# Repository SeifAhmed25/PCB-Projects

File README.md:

# Seif Ahmed - PCB Design Portfolio

This repository showcases my practical work in **PCB design**, focusing on **schematic creation**, **PCB layout**, and **manufacturing optimization** using **KiCad** software.

Projects are arranged from **latest to oldest**.

**Tools & Skills:**  
KiCad • Circuit Design • PCB Layout • DRC/ERC Checks • Soldering • Git Version Control • Documentation

---

## MCU Datalogger

**Goal:**  
Design a printed circuit board for a microcontroller-based data logger using the **ATmega328P-AU**, supported by two **EEPROMs** and a **real-time clock (RTC)**.

**Key Features:**
- Designed in two versions: a **2-layer** and a **4-layer** PCB, both managed using **Git** version control.  
- The **ATmega328P-AU** acts as the central controller.  
- Handles communication with the **RTC** and **EEPROM** modules.  
- Includes indicator LEDs and a reset circuit for the microcontroller.

**Main Components:**
- ATmega328P-AU  
- Crystal oscillator  
- Battery  
- Capacitors (decoupling)  
- Resistors  

**Project Pictures:**  
- **Board Schematic**  
    
- **Board Layout**  
    
- **Board Top View**  
    
- **Board Back View**  

---

## Solar Power Supply PCB

**Goal:**  
Design and implement a PCB that delivers a **regulated 3.3 V output** from a **solar panel**, functioning as a **solar energy regulator module**.  
This circuit was originally designed by *Elektor Magazine* and reimplemented in **KiCad**.

**Key Features:**
- Converts unregulated solar panel voltage into regulated **3.3 V**.  
- Suitable for powering **microcontrollers and sensors**.  
- Includes **copper fills** and a mix of **THT and SMD components**.

**Main Components:**
- Male connectors  
- Protection diodes  
- Inductor (switching regulator)  
- DC-DC converter  
- Resistors  

**Project Pictures:**  
- **Board Schematic**  
    
- **Board Top View**  
    
- **Board Back View**  

---

## Breadboard Power Supply PCB

**Goal:**  
Design a compact PCB that plugs directly into a **breadboard** and provides **5 V** and **3.3 V** regulated outputs.

**Key Features:**
- Fits perfectly on a standard breadboard.  
- Provides both **5 V** and **3.3 V** outputs.  
- Includes an **on/off switch** and **copper fills**.  
- Assembled using **THT components** for ease of soldering.

**Main Components:**
- Capacitors  
- LED  
- Jack connector  
- Screw terminals  
- Male connectors  
- Resistors  
- Slide switch  
- Voltage regulators  

**Project Pictures:**  
- **Board Schematic**  
    
- **Board Top View**  
    
- **Board Back View**  

---

## LED Torch PCB

**Goal:**  
An introductory project for learning **KiCad** fundamentals through schematic capture, PCB layout, and basic 3D visualization.

**Key Features:**
- Simple LED lighting circuit.  
- Demonstrates PCB routing and footprint placement.  
- Serves as a base for learning design rules and 3D viewer tools.

**Main Components:**
- Battery  
- Switch  
- Resistor  
- LED  

**Project Pictures:**  
- **Board Top View**  
    
- **Board Back View**  

---

**Author:** Seif Ahmed  
**Contact:** [Email](mailto:seif7760@gmail.com)  
**Software Used:** KiCad 9.0

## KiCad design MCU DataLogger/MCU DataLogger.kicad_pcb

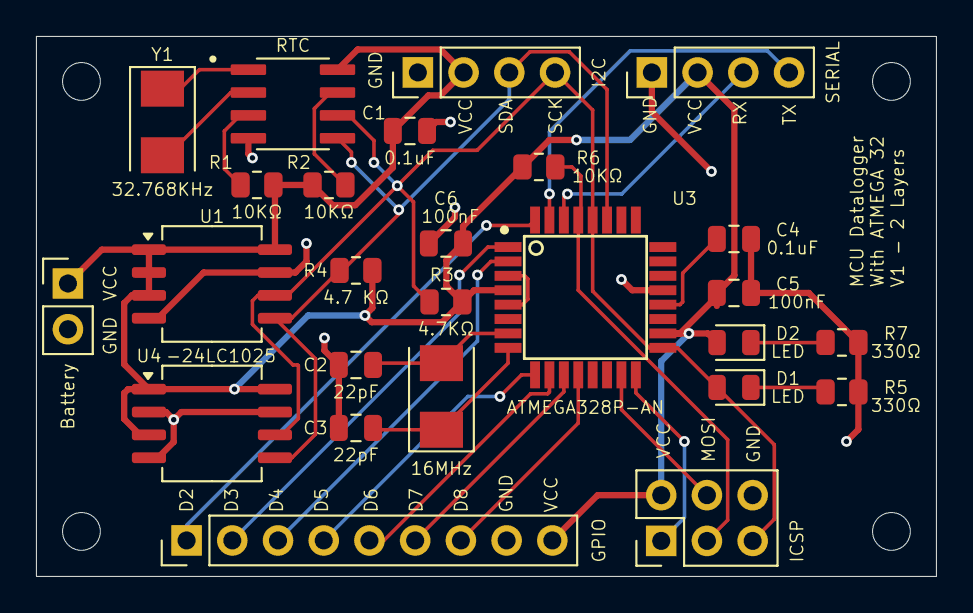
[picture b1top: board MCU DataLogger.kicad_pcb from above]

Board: 2 copper layers, 50.0 x 30.0 mm, 30 parts (0 on the bottom side), 26 nets.

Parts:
Battery: Battery; PinHeader_1x02_P2.54mm_Vertical
C1, C4: 0.1uF; C_0805_2012Metric
C2, C3: 22pF; C_0805_2012Metric
C5, C6: 100nF; C_0805_2012Metric
D1, D2: LED; LED_0805_2012Metric
GPIO: Conn_01x09_Pin; PinHeader_1x09_P2.54mm_Vertical
H1, H2, H3, H4: MountingHole; MountingHole_2.1mm
I2C: Conn_01x04_Pin; PinHeader_1x04_P2.54mm_Vertical
ICSP: Conn_02x03_Odd_Even; PinHeader_2x03_P2.54mm_Vertical
R1, R2, R6: 10KΩ; R_0805_2012Metric
R3: 4.7KΩ; R_0805_2012Metric
R4: 4.7 KΩ; R_0805_2012Metric
R5, R7: 330Ω; R_0805_2012Metric
RTC: DS1337S_; SOIC127P600X175-8N
SERIAL: Conn_01x04_Pin; PinHeader_1x04_P2.54mm_Vertical
U1, U4: -24LC1025; SOIC-8_5.3x6.2mm_P1.27mm
U3: ATMEGA328P-AN; QFP80P900X900X120-32N
Y1: 32.768KHz; Crystal_SMD_5032-2Pin_5.0x3.2mm
Y2: 16MHz; Crystal_SMD_5032-2Pin_5.0x3.2mm

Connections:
/D2: GPIO.1, U3.32 (PD2)
/D3: GPIO.2, U3.1 (PD3)
/D4: GPIO.3, U3.2 (PD4)
/D5: GPIO.4, U3.9 (PD5)
/D6: GPIO.5, U3.10 (PD6)
/D7: GPIO.6, U3.11 (PD7)
/D8: GPIO.7, U3.12 (PB0)
/MISO: ICSP.1, U3.16 (PB4)
/MOSI: ICSP.4, U3.15 (PB3)
/RESET: ICSP.3, R6.1, U3.29 (PC6/~RESET)
/RX: SERIAL.3, U3.30 (PD0)
/SCK: D1.2 (A), I2C.4, ICSP.5, R3.2, RTC.6 (SCL), U1.6 (SCL), U3.17 (PB5), U3.28 (PC5), U4.6 (SCL)
/SDA: I2C.3, R4.2, RTC.5 (SDA), U1.5 (SDA), U3.27 (PC4), U4.5 (SDA)
/TX: SERIAL.4, U3.31 (PD1)
/VCC: Battery.1 (+), C1.1, C5.1, C6.1, D2.2 (A), GPIO.9, I2C.2, ICSP.2, R1.1, R2.1, R3.1, R4.1, R6.2, RTC.8 (VCC), SERIAL.2, U1.1 (A0), U1.2 (A1), U1.3 (A2), U1.8 (VCC), U3.4 (VCC), U3.18 (AVCC), U4.1 (A0), U4.3 (A2), U4.8 (VCC)
GND: Battery.2 (-), C1.2, C2.1, C3.1, C4.1, C5.2, C6.2, GPIO.8, I2C.1, ICSP.6, R5.1, R7.2, RTC.4 (GND), SERIAL.1, U1.4 (GND), U1.7 (WP), U3.21 (GND), U4.2 (A1), U4.4 (GND), U4.7 (WP)
unnamed: D1.1 (K), R5.2
unnamed: D2.1 (K), R7.1
unnamed: R2.2, RTC.7 (SQW/~INT)
unnamed: RTC.1 (X1), Y1.1
unnamed: RTC.2 (X2), Y1.2
unnamed: R1.2, RTC.3 (~INTA)
unnamed: C4.2, U3.20 (AREF)
unnamed: U3.3 (GND), U3.5 (GND)
unnamed: C2.2, U3.7 (PB6), Y2.2
unnamed: C3.2, U3.8 (PB7), Y2.1

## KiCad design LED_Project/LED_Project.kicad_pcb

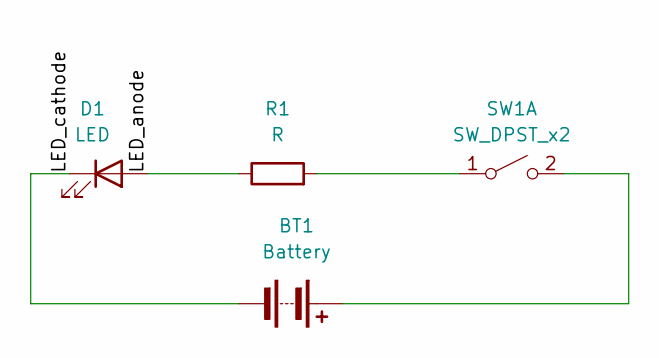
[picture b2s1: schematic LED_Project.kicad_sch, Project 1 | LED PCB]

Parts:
BT1: Battery; BatteryHolder_Keystone_105_1x2430
D1: LED; LED_D5.0mm
R1: R; R_Axial_DIN0204_L3.6mm_D1.6mm_P7.62mm_Horizontal
SW1: SW_DPST_x2; SW_TH_Tactile_Omron_B3F-10xx

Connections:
/LED_anode: D1.2 (A), R1.1
/LED_cathode: BT1.2 (-), D1.1 (K)
unnamed: BT1.1 (+), SW1.2 (B)
unnamed: R1.2, SW1.1 (A)

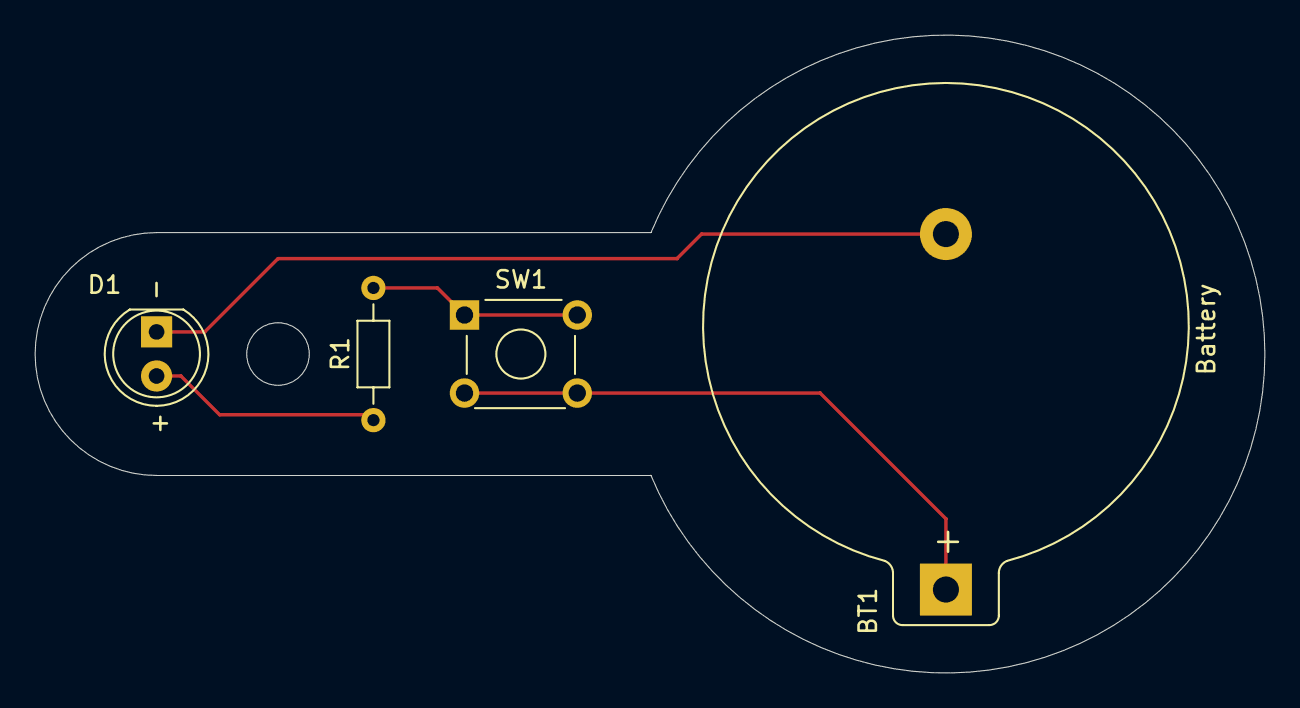
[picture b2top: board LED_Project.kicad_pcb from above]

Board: 2 copper layers, 70.9 x 36.8 mm, 4 parts (0 on the bottom side), 4 nets.

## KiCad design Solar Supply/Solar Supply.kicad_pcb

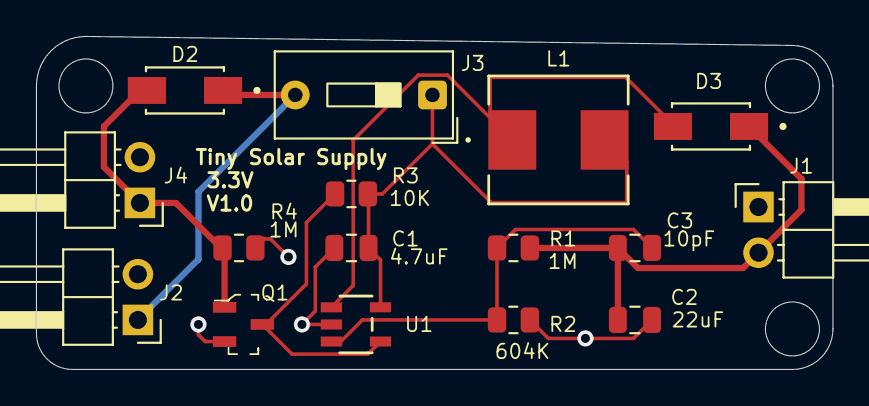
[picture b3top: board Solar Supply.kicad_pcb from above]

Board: 2 copper layers, 44.2 x 18.5 mm, 16 parts (0 on the bottom side), 8 nets.

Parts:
C1: 4.7uF; C_0805_2012Metric
C2: 22uF; C_0805_2012Metric
C3: 10pF; C_0805_2012Metric
D2, D3: SS14; DIOM4325X250N
J1, J2, J4: Conn_01x02_Pin; PinHeader_1x02_P2.54mm_Horizontal
J3: Conn_01x02_Pin; SW_DIP_SPSTx01_Slide_9.78x4.72mm_W7.62mm_P2.54mm
L1: ASPI-0630LR-100M-T15; IND_ASPI-0630LR_ABR
Q1: 2N7002; SOT-23-3
R1, R4: 1M; R_0805_2012Metric
R2: 604K; R_0805_2012Metric
R3: 10K; R_0805_2012Metric
U1: AP3015AKTR-G1; SOT23-5_1P55X2P9_DIO

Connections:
/Battery_P: D2.C, J2.1, J3.2
/Out_P: C2.1, C3.1, D3.C, J1.2, R1.1
/Solar_P: D2.A, J4.1, Q1.1 (G), R4.1
GNDD: C1.2, C2.2, J1.1, J2.2, J4.2, Q1.2 (S), R2.2, R4.2, U1.2 (GND)
unnamed: C1.1, J3.1, L1.2, R3.1, U1.5 (VIN)
unnamed: Q1.3 (D), R3.2, U1.4 (SHDN)
unnamed: C3.2, R1.2, R2.1, U1.3 (FB)
unnamed: D3.A, L1.1, U1.1 (SW)

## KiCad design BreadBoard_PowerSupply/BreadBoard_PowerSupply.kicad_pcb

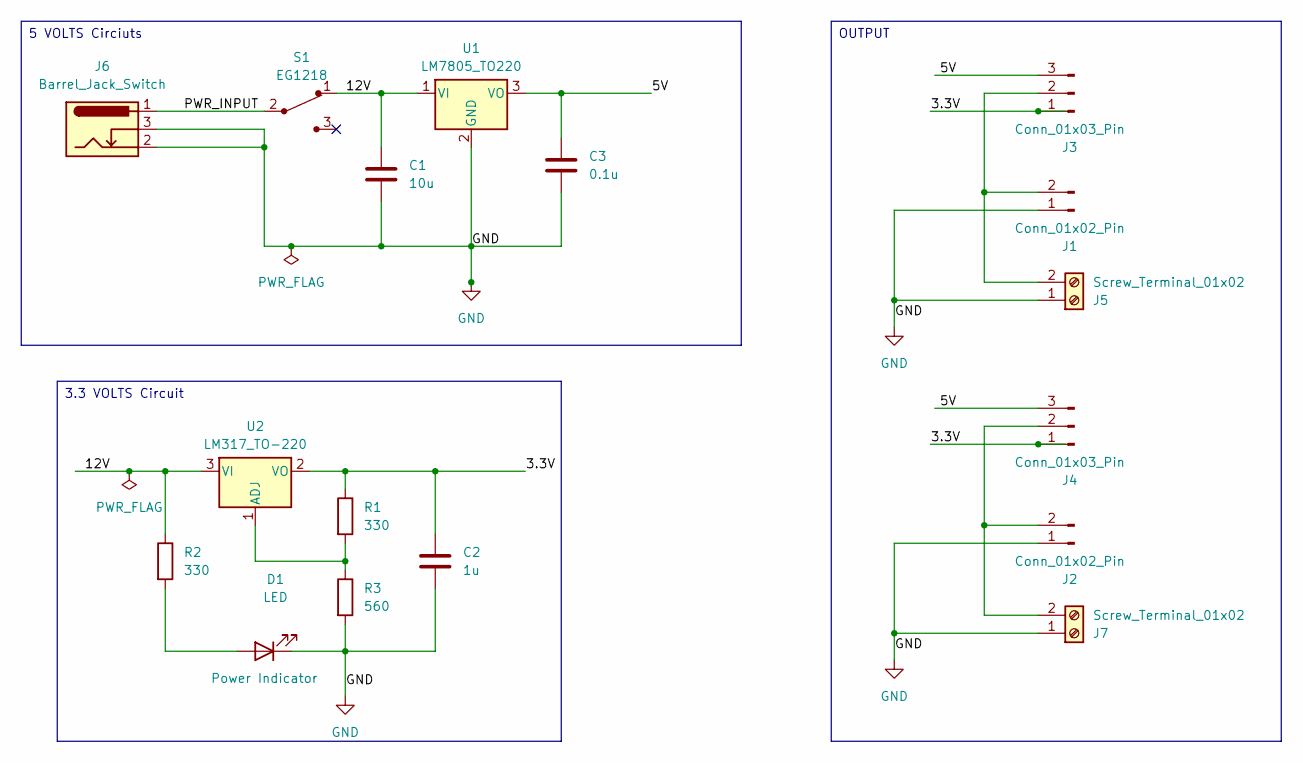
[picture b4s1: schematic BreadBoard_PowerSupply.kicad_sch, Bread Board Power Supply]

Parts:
C1: 10u; C_Disc_D3.0mm_W1.6mm_P2.50mm
C2: 1u; C_Disc_D3.0mm_W1.6mm_P2.50mm
C3: 0.1u; C_Disc_D3.0mm_W1.6mm_P2.50mm
D1: LED; LED_D5.0mm
J1, J2: Conn_01x02_Pin; PinHeader_1x02_P2.54mm_Vertical
J3, J4: Conn_01x03_Pin; PinHeader_1x03_P2.54mm_Vertical
J5, J7: Screw_Terminal_01x02; TerminalBlock_bornier-2_P5.08mm
J6: Barrel_Jack_Switch; BarrelJack_Horizontal
R1, R2: 330; R_Axial_DIN0204_L3.6mm_D1.6mm_P7.62mm_Horizontal
R3: 560; R_Axial_DIN0204_L3.6mm_D1.6mm_P7.62mm_Horizontal
S1: EG1218; Switch_Slide_11.6x4mm_EG1218; MPN EG1218; Digi-Key_PN EG1903-ND
U1: LM7805_TO220; TO-220-3_Vertical
U2: LM317_TO-220; TO-220-3_Vertical

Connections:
/3.3V: C2.1, J3.1, J4.1, R1.1, U2.2 (VO)
/5V: C3.2, J3.3, J4.3, U1.3 (VO)
/12V: C1.2, R2.1, S1.1, U1.1 (VI), U2.3 (VI)
/PWR_INPUT: J6.1, S1.2
GND: C1.1, C2.2, C3.1, D1.1 (K), J1.1, J2.1, J5.1, J6.2, J6.3, J7.1, R3.2, U1.2 (GND)
unnamed: D1.2 (A), R2.2
unnamed: J1.2, J3.2, J5.2
unnamed: J2.2, J4.2, J7.2
unnamed: R1.2, R3.1, U2.1 (ADJ)

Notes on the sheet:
5 VOLTS Circiuts
OUTPUT
3.3 VOLTS Circuit

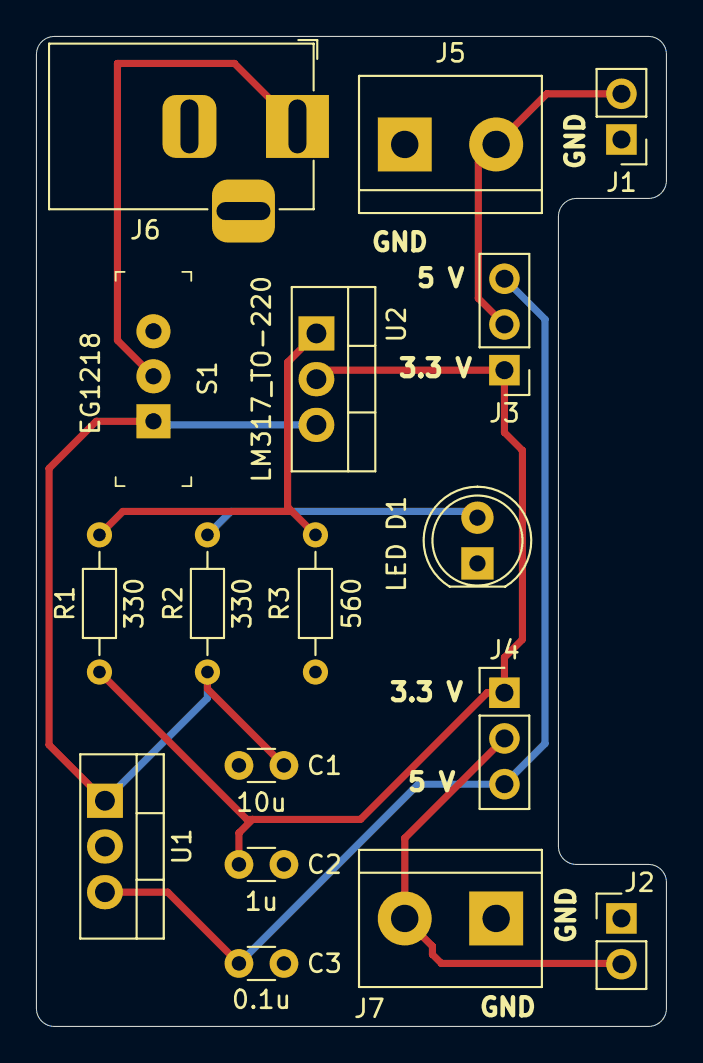
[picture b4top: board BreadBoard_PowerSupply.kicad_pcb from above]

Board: 2 copper layers, 35.0 x 55.0 mm, 17 parts (0 on the bottom side), 9 nets.

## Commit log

2025-10-15 First 3 Projects
2025-10-19 FootPrints Added
2025-10-19 MCU Datalogger Project Schematic Complete
2025-10-19 MCU Datalogger Project 2 Layers V1 Completed
2025-10-21 MCU DataLogger Enhance 2Layers Version
2025-10-21 BoardsPics_Folder_Added
2025-10-21 MCU Datalogger Board Pics added
2025-10-21 MCU_Datalogger_Layout_Pic_added
2025-10-21 MCU Datalogger Layout pic added
2025-10-21 Enhance README file for clarity.md
